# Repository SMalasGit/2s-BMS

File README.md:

This chip is rated for 1-2s (cell) operation with lithium ion or lithium polymer batteries. This BMS config is set up for a 5 amp charging current at an 8.4 voltage running, which is supplied via the USB-C port of the BMS. This BMS has built in trip current of 35 amps, and a physical fuse onboard for currents exceeding 25 amps. This helps ensure the safety of the device and battery pack

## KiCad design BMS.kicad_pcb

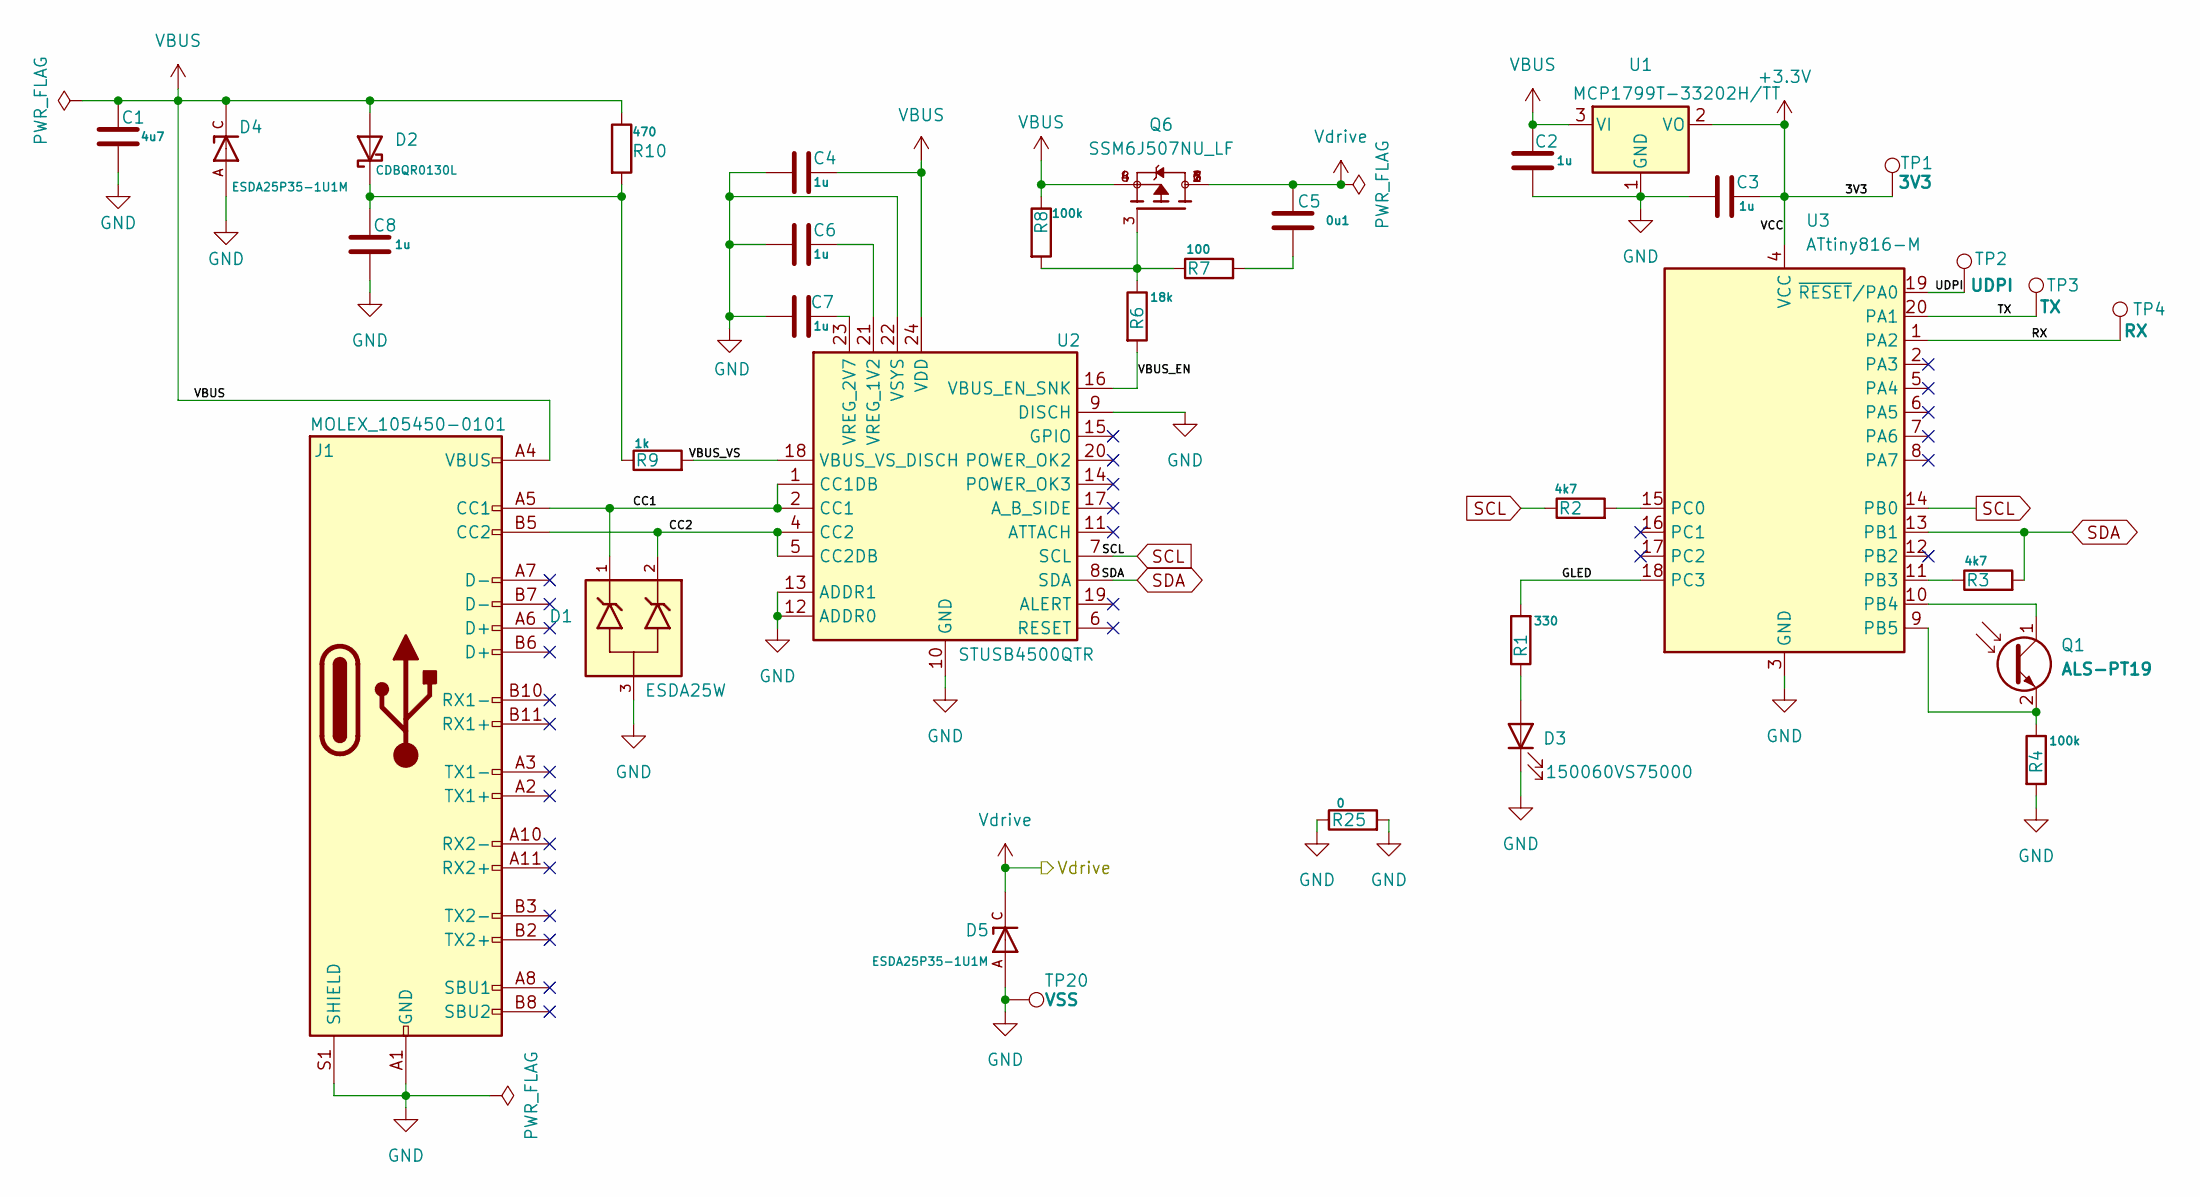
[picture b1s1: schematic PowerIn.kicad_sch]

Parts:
C1: 4u7; C_0603_1608Metric
C2, C3, C4, C6, C7, C8: 1u; C_0402_1005Metric
C5: 0u1; C_0402_1005Metric
D1: ESDA25W; SOT65P210X110-3N; PARTREV 2
D2: CDBQR0130L; D_0402_1005Metric
D3: 150060VS75000; LED_0603_1608Metric
D4, D5: ESDA25P35-1U1M; TVS_ESDA25P35-1U1M; PARTREV 2
J1: MOLEX_105450-0101; USB_C_Receptacle_Molex_105450-0101
Q1: ALS-PT19; LED_0603_1608Metric
Q6: SSM6J507NU_LF; TRANS_SSM6J507NU_LF; PARTREV 2.0
R1: 330; R_0603_1608Metric
R2, R3: 4k7; R_0402_1005Metric
R4, R8: 100k; R_0402_1005Metric
R6: 18k; R_0402_1005Metric
R7: 100; R_0402_1005Metric
R9: 1k; R_0402_1005Metric
R10: 470; R_0402_1005Metric
R25: 0; R_0201_0603Metric
TP1: 3V3; test
TP2: UDPI; test
TP3: TX; test
TP4: RX; test
TP20: VSS; PinHeader_1x01_P1.00mm_Vertical
U1: MCP1799T-33202H/TT; SOT-23
U2: STUSB4500QTR; QFN-24-1EP_4x4mm_P0.5mm_EP2.7x2.7mm
U3: ATtiny816-M; VQFN-20-1EP_3x3mm_P0.4mm_EP1.7x1.7mm

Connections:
+3.3V: C3.2, TP1.1, U1.2 (VO), U3.4 (VCC)
/PowerIn/CC1: D1.1, J1.A5 (CC1), U2.1 (CC1DB), U2.2 (CC1)
/PowerIn/CC2: D1.2, J1.B5 (CC2), U2.4 (CC2), U2.5 (CC2DB)
/PowerIn/GLED: R1.2, U3.18 (PC3)
/PowerIn/RX: TP4.1, U3.1 (PA2)
/PowerIn/TX: TP3.1, U3.20 (PA1)
/PowerIn/UDPI: TP2.1, U3.19 (~RESET/PA0)
/PowerIn/VBUS_EN: R6.2, U2.16 (VBUS_EN_SNK)
/PowerIn/VBUS_VS: R9.2, U2.18 (VBUS_VS_DISCH)
GND: C1.2, C2.1, C3.1, C4.1, C6.1, C7.1, C8.2, D1.3, D3.1 (K), D4.A, D5.A, J1.A1 (GND), J1.A12 (GND), J1.B1 (GND), J1.B12 (GND), J1.S1 (SHIELD), R4.2, R25.1, R25.2, TP20.1, U1.1 (GND), U2.9 (DISCH), U2.10 (GND), U2.12 (ADDR0), U2.13 (ADDR1), U2.22 (VSYS), U2.25 (GND), U3.3 (GND), U3.21 (GND); also elsewhere on the board
unnamed: C5.1, R7.2
unnamed: C8.1, D2.1 (K), R9.1, R10.2
unnamed: D3.2 (A), R1.1
unnamed: Q1.1 (C), U3.10 (PB4)
unnamed: Q1.2 (E), R4.1, U3.9 (PB5)
unnamed: Q6.3, R6.1, R7.1, R8.2
unnamed: C6.2, U2.21 (VREG_1V2)
unnamed: C7.2, U2.23 (VREG_2V7)
unnamed: R3.1, U3.11 (PB3)
unnamed: R2.2, U3.15 (PC0)
SCL: R2.1, U2.7 (SCL), U3.14 (PB0)
SDA: R3.2, U2.8 (SDA), U3.13 (PB1)
VBUS: C1.1, C2.2, C4.2, D2.2 (A), D4.C, J1.A4 (VBUS), J1.A9 (VBUS), J1.B4 (VBUS), J1.B9 (VBUS), Q6.4, Q6.8, R8.1, R10.1, U1.3 (VI), U2.24 (VDD)
Vdrive: C5.2, D5.C, Q6.1, Q6.2, Q6.5, Q6.6, Q6.7; also elsewhere on the board

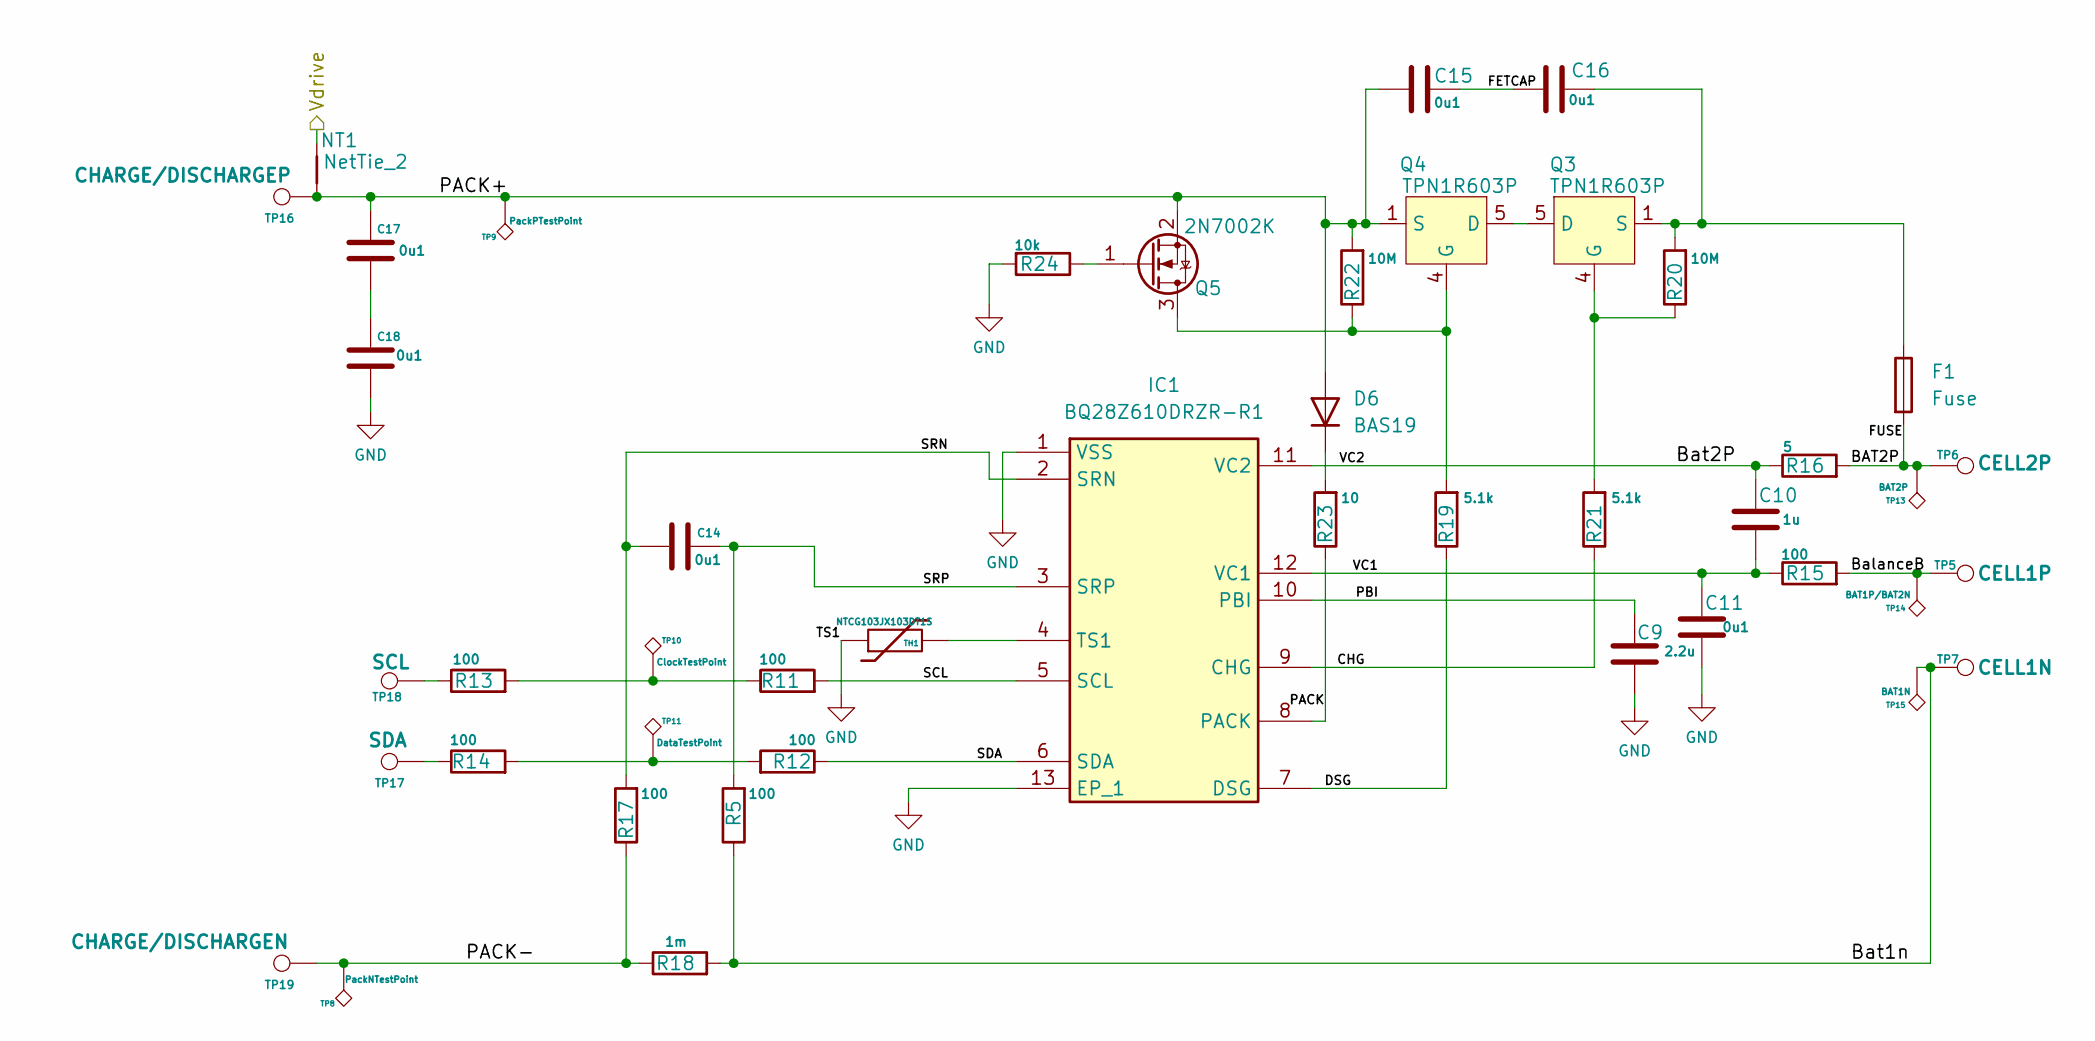
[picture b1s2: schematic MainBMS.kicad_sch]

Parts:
C9: 2.2u; C_0402_1005Metric
C10: 1u; C_0402_1005Metric
C11, C14, C15, C16, C17, C18: 0u1; C_0402_1005Metric
D6: BAS19; SOT-23
F1: Fuse; Fuse_1206_3216Metric
IC1: BQ28Z610DRZR-R1; IC_BQ27441DRZR-G1A; Mouser Part Number 595-BQ28Z610DRZR-R1
NT1: NetTie_2; NetTie-2_SMD_Pad0.5mm
Q3, Q4: TPN1R603P; TPN1R603PLL1Q
Q5: 2N7002K; SOT-23
R5, R11, R12, R13, R14, R15, R17: 100; R_0402_1005Metric
R16: 5; R_0402_1005Metric
R18: 1m; R_2010_5025Metric
R19, R21: 5.1k; R_0402_1005Metric
R20, R22: 10M; R_0603_1608Metric
R23: 10; R_0402_1005Metric
R24: 10k; R_0402_1005Metric
TH1: NTCG103JX103DT1S; R_0402_1005Metric
TP5: CELL1P; TestPoint_Pad_D1.5mm
TP6: CELL2P; TestPoint_Pad_D2.0mm
TP7: CELL1N; TestPoint_Pad_D2.0mm
TP8: PackNTestPoint; test
TP9: PackPTestPoint; test
TP10: ClockTestPoint; test
TP11: DataTestPoint; test
TP13: BAT2P; test
TP14: BAT1P/BAT2N; test
TP15: BAT1N; test
TP16: CHARGE/DISCHARGEP; TestPoint_Pad_D2.0mm
TP17: SDA; PinHeader_1x01_P1.00mm_Vertical
TP18: SCL; PinHeader_1x01_P1.00mm_Vertical
TP19: CHARGE/DISCHARGEN; TestPoint_Pad_D2.0mm

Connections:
/MainBMS/BAT2P: F1.2, R16.2, TP6.1, TP13.1
/MainBMS/BalanceB: R15.2, TP5.1, TP14.1
/MainBMS/Bat1n: R5.1, R18.2, TP7.1, TP15.1
/MainBMS/Bat2P: C10.2, IC1.11 (VC2), R16.1
/MainBMS/CHG: IC1.9 (CHG), R21.1
/MainBMS/DSG: IC1.7 (DSG), R19.1
/MainBMS/FETCAP: C15.1, C16.2
/MainBMS/PACK: IC1.8 (PACK), R23.1
/MainBMS/PACK+: C15.2, C17.1, D6.1 (A), NT1.1, Q4.1 (S), Q4.2 (S), Q4.3 (S), Q5.2 (S), R22.2, TP9.1, TP16.1
/MainBMS/PACK-: R17.1, R18.1, TP8.1, TP19.1
/MainBMS/PBI: C9.2, IC1.10 (PBI)
/MainBMS/SCL: IC1.5 (SCL), R11.2
/MainBMS/SDA: IC1.6 (SDA), R12.1
/MainBMS/SRN: C14.2, IC1.2 (SRN), R17.2
/MainBMS/SRP: C14.1, IC1.3 (SRP), R5.2
/MainBMS/VC1: C10.1, C11.2, IC1.12 (VC1), R15.1
GND: C9.1, C11.1, C18.2, IC1.1 (VSS), IC1.13 (EP_1), IC1.14 (EP_2), IC1.15 (EP_3), R24.2, TH1.1; also elsewhere on the board
unnamed: C16.1, F1.1, Q3.1 (S), Q3.2 (S), Q3.3 (S), R20.2
unnamed: C17.2, C18.1
unnamed 29: R11.1, R13.2, TP10.1; also elsewhere on the board
unnamed 30: R12.2, R14.2, TP11.1; also elsewhere on the board
unnamed: D6.3 (K), R23.2
unnamed: IC1.4 (TS1), TH1.2
unnamed: Q3.5 (D), Q3.6 (D), Q3.7 (D), Q3.8 (D), Q3.9 (D), Q4.5 (D), Q4.6 (D), Q4.7 (D), Q4.8 (D), Q4.9 (D)
unnamed: Q3.4 (G), R20.1, R21.2
unnamed: Q4.4 (G), Q5.3 (D), R19.2, R22.1
unnamed: Q5.1 (G), R24.1
unnamed: R13.1, TP18.1
unnamed: R14.1, TP17.1
Vdrive: NT1.2; also elsewhere on the board

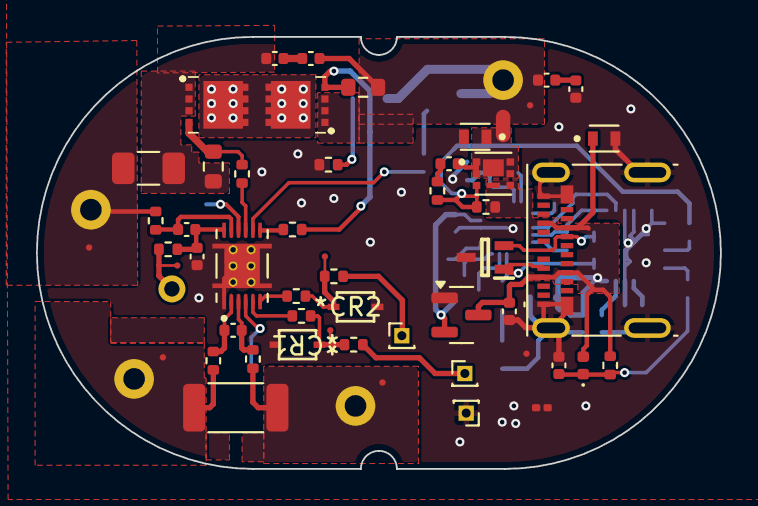
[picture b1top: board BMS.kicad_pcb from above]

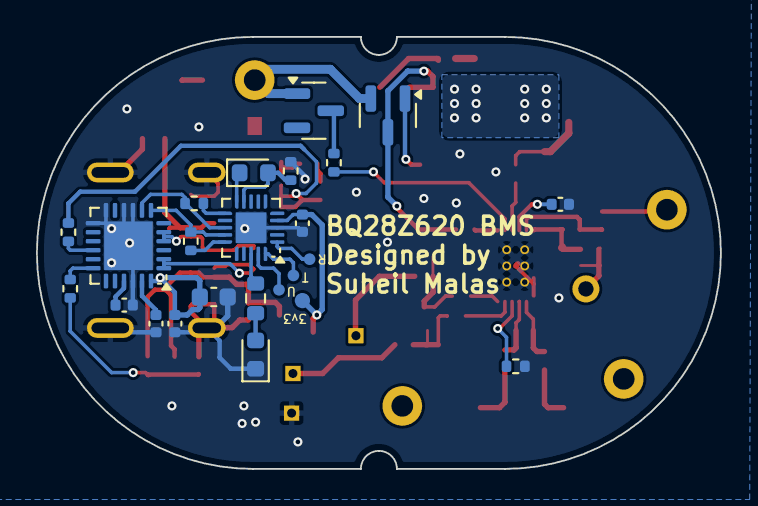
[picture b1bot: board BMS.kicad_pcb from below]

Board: 2 copper layers, 38.0 x 24.0 mm, 82 parts (24 on the bottom side), 52 nets.

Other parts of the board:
CR1, CR2: MM3Z5V6C; ZDO_MM3Z5V6C_OSI
TP12: GndATestPoint; test

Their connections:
GND: CR1.2, CR2.2, TP12.1; also elsewhere on the board
unnamed 29: CR1.1; also elsewhere on the board
unnamed 30: CR2.1; also elsewhere on the board
